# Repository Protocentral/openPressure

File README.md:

# Protocentral OpenPressure

OpenPressure is a result of our work in trying to interface pressure sensors to an ADC as well as a display system based on Arduino. We found the ADS1220 to be a great chip that can directly take a 4-wire, 3-wire or a 2-wire sensor and give the digital output. 

Combine this powerful functionality with an ATSAMD21 micro-controller and you've got your very own Arduino-compatible pressure and temperature sensor interface system.

Features
--------
* TI ADS1220 24-bit ADC
* 4-wire sensor can be interfaced directly to the inputs
* On-board 5V band-gap voltage reference
* ATSAMD21 microcontroller loaded with Arduino M0/Zero bootloader
* Programmable with the Arduino IDE
* USB CDC Interface for data transfer
* "Cap" compatibility to add Bluetooth/WiFi/SD Card interfaces
* On-board 3.7V Li-Poly battery with charger
* On-board Boost DC/DC converter 

Repository Contents
-------------------
* **/hardware** - All Eagle design files (.brd, .sch)
* **/software** - Arduino libraries and example code
* **/docs** - Additional Documentation

Board Overview
--------------

How to setup Arduino support for openPressure
---------------------------------------------------
OpenPressure is powered by the Arduino Zero board support file.The first thing you will need to do is to download the latest release of the Arduino IDE. You will need to be using version 1.6.4 or higher. 

If you want to program your Zero while offline you need to install the Arduino Desktop IDE and add the Atmel SAMD Core to it. This simple procedure is done selecting Tools menu, then Boards and last Boards Manager, as documented in the Arduino Boards Manager page. 

* Select Tools > Board > Board Manager
* You should find Arduino SAMD(32-bit ARM cortex-M0+) boards listed in the Board Manager window.

* Click the “Install” button on the chosen category.The download process will begin and install the toolchain for SAMD microcontrollers.
* Restart Arduino and look under Tools > Boards and you should see the addition of the Arduino boards in your board list.

Setup Arduino Sketch
--------------------
We have provided a few Arduino sketch examples . They are designed to work right away with no changes. To make the examples work with your board, you simply need to upload the code to your board.

License Information
-------------------
This product is open source!

Please use, reuse, and modify these files as you see fit. Please maintain attribution to Protocentral and release anything derivative under the same license.

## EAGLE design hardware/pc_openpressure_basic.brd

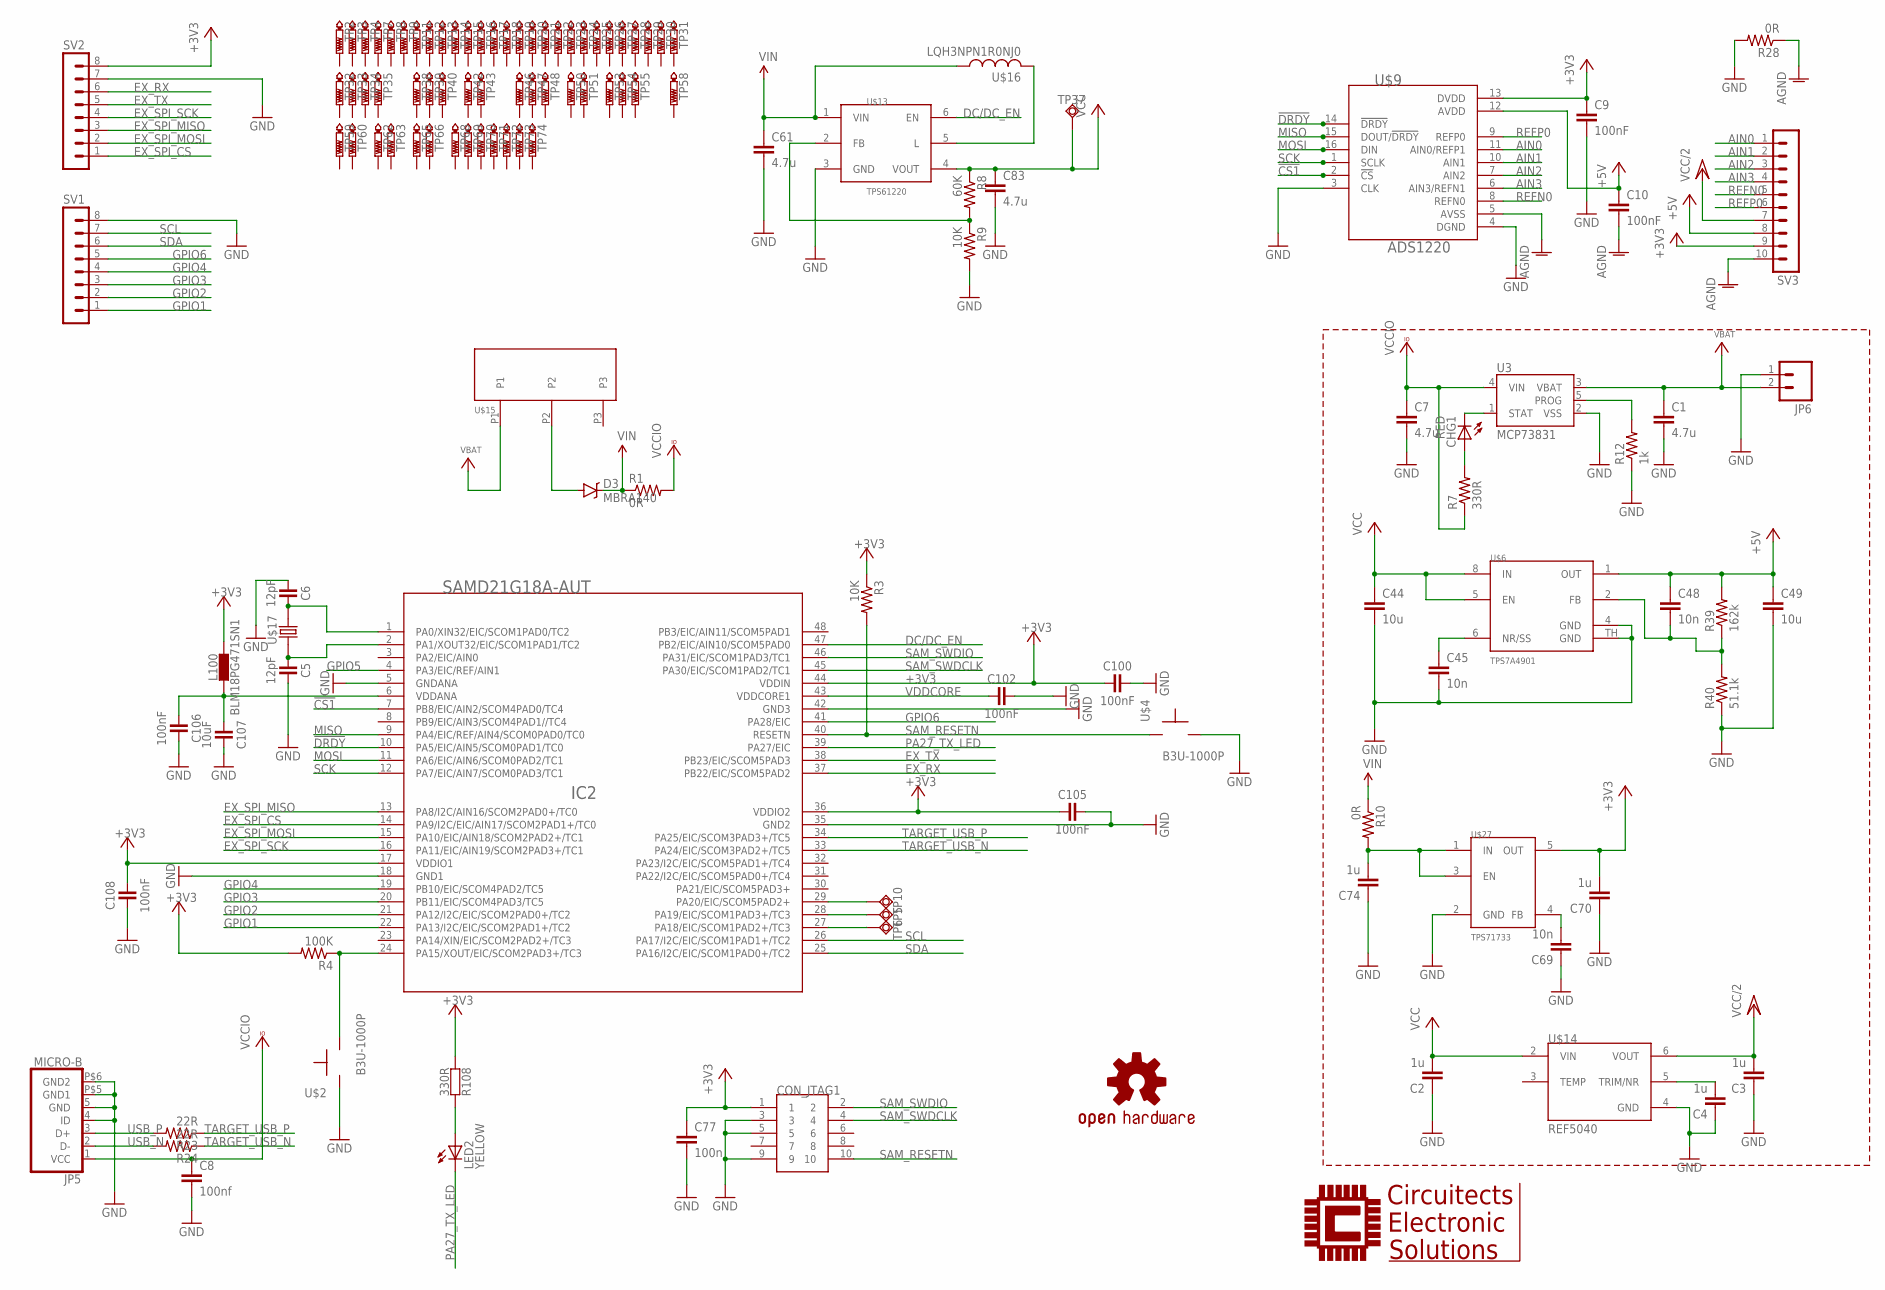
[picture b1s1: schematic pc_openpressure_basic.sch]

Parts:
C1, C7, C61, C83: 4.7u; C0805
C2, C3, C4, C70, C74: 1u; C0805
C5, C6: 12pF; C0402
C8: 100nf; C0805
C9, C10, C100, C102, C105, C106, C108: 100nF; C0805
C44, C49: 10u; C0805
C45, C48, C69: 10n; C0402
C77: 100n; C0805
C107: 10uF; C0805
CHG1: RED; CHIPLED_0603
CON_JTAG1: HDR-SMT-50MIL/5X2
D3: MBRA140; SMA-DIODE
IC2: SAMD21G18A-AUT; TQFP48
JP5: MICRO-B
JP6: M02-JST-2MM-SMT; JST-2-SMD
L100: BLM18PG471SN1; C0603
LED2: YELLOW; CHIPLED_0603
R1, R10: 0R; R0402
R3, R9: 10K; R0805
R4: 100K; R0402
R7: 330R; R0805
R8: 60K; R0805
R12: 1k; R0805
R23, R24: 22R; R0402
R28: 0R; R0805
R39: 162k; R0805
R40: 51.1k; R0805
R108: 330R; C0402
SV1, SV2: MA08-1
SV3: MA10-1
TP2, TP3, TP4, TP7, TP8, TP9, TP11, TP12, TP13, TP14, TP15, TP16, TP17, TP18, TP19, TP20, TP21, TP22, TP23, TP24, TP25, TP26, TP27, TP28, TP29, TP30, TP31, TP32, TP33, TP34, TP35, TP38, TP39, TP40, TP42, TP43, TP46, TP47, TP48, TP50, TP51, TP53, TP54, TP55, TP58, TP59, TP60, TP62, TP63, TP65, TP66, TP68, TP69, TP70, TP71, TP72, TP73, TP74: PTR1PAD1-13; P1-13
TP5, TP6, TP10, TP37: TPSQB1,27; B1,27
U3: MCP73831; SOT23-5
U$2, U$4: B3U-1000P
U$6: TPS7A4901; S-PDSO-G08
U$7: CES-LOGO; CES-LOGO-SMALL
U$8: PROTY-LOGO; LOGO-PROTY
U$9: ADS1220; TSSOP-16
U$13: TPS61220; SC-70-6
U$14: REF5040; SO-08M
U$15: PCM12SMTR
U$16: LQH3NPN1R0NJ0; LQH3NP
U$17: ECS-X-34B; ECX-31B
U$18: PROTY_LOGO_WITH_TEXT; PROTY_WITH_TEXT
U$19: OSHW-LOGOM; OSHW-LOGO-M
U$27: TPS71733; SC70-5

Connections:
!CS1: IC2.7 (PB8/EIC/AIN2/SCOM4PAD0/TC4), U$9.2 (!CS)
!DRDY: IC2.10 (PA5/EIC/AIN5/SCOM0PAD1/TC0), U$9.14 (!DRDY)
+3V3: C9.1, C70.2, C77.1, C100.1, C105.1, C108.2, CON_JTAG1.1, IC2.17 (VDDIO1), IC2.36 (VDDIO2), IC2.44 (VDDIN), L100.2, R3.1, R4.2, R108.1, SV2.8, SV3.9, U$9.13 (DVDD), U$27.5 (OUT)
+5V: C10.1, C48.1, C49.1, R39.2, SV3.8, U$6.1 (OUT), U$9.12 (AVDD)
AGND: C10.2, R28.1, SV3.10, U$9.5 (AVSS)
AIN0: SV3.1, U$9.11 (AIN0/REFP1)
AIN1: SV3.2, U$9.10 (AIN1)
AIN2: SV3.3, U$9.7 (AIN2)
AIN3: SV3.4, U$9.6 (AIN3/REFN1)
DC/DC_EN: IC2.47 (PB2/EIC/AIN10/SCOM5PAD0), U$13.6 (EN)
EX_RX: IC2.37 (PB22/EIC/SCOM5PAD2), SV2.6
EX_SPI_CS: IC2.14 (PA9/I2C/EIC/AIN17/SCOM2PAD1+/TC0), SV2.1
EX_SPI_MISO: IC2.13 (PA8/I2C/AIN16/SCOM2PAD0+/TC0), SV2.3
EX_SPI_MOSI: IC2.15 (PA10/EIC/AIN18/SCOM2PAD2+/TC1), SV2.2
EX_SPI_SCK: IC2.16 (PA11/EIC/AIN19/SCOM2PAD3+/TC1), SV2.4
EX_TX: IC2.38 (PB23/EIC/SCOM5PAD3), SV2.5
GND: C1.2, C2.1, C3.1, C4.1, C5.2, C6.1, C7.2, C8.2, C9.2, C44.2, C45.2, C49.2, C61.2, C69.1, C70.1, C74.1, C77.2, C83.2, C100.2, C102.2, C105.2, C106.2, C107.2, C108.1, CON_JTAG1.3, CON_JTAG1.5, CON_JTAG1.9, IC2.5 (GNDANA), IC2.18 (GND1), IC2.35 (GND2), IC2.42 (GND3), JP5.4 (ID), JP5.5 (GND), JP5.P$5 (GND1), JP5.P$6 (GND2), JP6.1, R9.2, R12.1, R28.2, R40.1, SV1.8, SV2.7, U3.2 (VSS), U$2.P$1, U$4.P$2, U$6.4 (GND), U$6.TH (GND), U$9.3 (CLK), U$9.4 (DGND), U$13.3 (GND), U$14.4 (GND), U$27.2 (GND)
GPIO1: IC2.22 (PA13/I2C/EIC/SCOM2PAD1+/TC2), SV1.1
GPIO2: IC2.21 (PA12/I2C/EIC/SCOM2PAD0+/TC2), SV1.2
GPIO3: IC2.20 (PB11/EIC/SCOM4PAD3/TC5), SV1.3
GPIO4: IC2.19 (PB10/EIC/SCOM4PAD2/TC5), SV1.4
GPIO5: IC2.4 (PA3/EIC/REF/AIN1)
GPIO6: IC2.41 (PA28/EIC), SV1.5
MISO: IC2.9 (PA4/EIC/REF/AIN4/SCOM0PAD0/TC0), U$9.15 (DOUT/!DRDY)
MOSI: IC2.11 (PA6/EIC/AIN6/SCOM0PAD2/TC1), U$9.16 (DIN)
unnamed: C6.2, IC2.1 (PA0/XIN32/EIC/SCOM1PAD0/TC2), U$17.P$2 (2)
unnamed: C74.2, R10.2, U$27.1 (IN), U$27.3 (EN)
unnamed: D3.A, U$15.P2
unnamed: R8.2, R9.1, U$13.2 (FB)
unnamed: IC2.24 (PA15/XOUT/EIC/SCOM2PAD3+/TC3), R4.1, U$2.P$2
unnamed: C5.1, IC2.2 (PA1/XOUT32/EIC/SCOM1PAD1/TC2), U$17.P$1 (1)
unnamed: C106.1, C107.1, IC2.6 (VDDANA), L100.1
unnamed: IC2.27 (PA18/EIC/SCOM1PAD2+/TC3), TP6.TP
unnamed: CHG1.C, U3.1 (STAT)
unnamed: CHG1.A, R7.2
unnamed: C45.1, U$6.6 (NR/SS)
unnamed: IC2.28 (PA19/EIC/SCOM1PAD3+/TC3), TP5.TP
unnamed: IC2.29 (PA20/EIC/SCOM5PAD2+), TP10.TP
unnamed: R12.2, U3.5 (PROG)
unnamed: LED2.A, R108.2
unnamed: C48.2, R39.1, R40.2, U$6.2 (FB)
unnamed: C4.2, U$14.5 (TRIM/NR)
unnamed: U$13.5 (L), U$16.P$2 (2)
unnamed: C69.2, U$27.4 (FB)
PA27_TX_LED: IC2.39 (PA27/EIC), LED2.C
REFN0: SV3.5, U$9.8 (REFN0)
REFP0: SV3.6, U$9.9 (REFP0)
SAM_RESETN: CON_JTAG1.10, IC2.40 (RESETN), R3.2, U$4.P$1
SAM_SWDCLK: CON_JTAG1.4, IC2.45 (PA30/EIC/SCOM1PAD2/TC1)
SAM_SWDIO: CON_JTAG1.2, IC2.46 (PA31/EIC/SCOM1PAD3/TC1)
SCK: IC2.12 (PA7/EIC/AIN7/SCOM0PAD3/TC1), U$9.1 (SCLK)
SCL: IC2.26 (PA17/I2C/EIC/SCOM1PAD1+/TC2), SV1.7
SDA: IC2.25 (PA16/I2C/EIC/SCOM1PAD0+/TC2), SV1.6
TARGET_USB_N: IC2.33 (PA24/EIC/SCOM3PAD2+/TC5), R24.1
TARGET_USB_P: IC2.34 (PA25/EIC/SCOM3PAD3+/TC5), R23.1
USB_N: JP5.2 (D-), R24.2
USB_P: JP5.3 (D+), R23.2
VBAT: C1.1, JP6.2, U3.3 (VBAT), U$15.P1
VCC: C2.2, C44.1, C83.1, R8.1, TP37.TP, U$6.5 (EN), U$6.8 (IN), U$13.4 (VOUT), U$14.2 (VIN)
VCC/2: C3.2, SV3.7, U$14.6 (VOUT)
VCCIO: C7.1, C8.1, JP5.1 (VCC), R1.2, R7.1, U3.4 (VIN)
VDDCORE: C102.1, IC2.43 (VDDCORE1)
VIN: C61.1, D3.C, R1.1, R10.1, U$13.1 (VIN), U$16.P$1 (1)

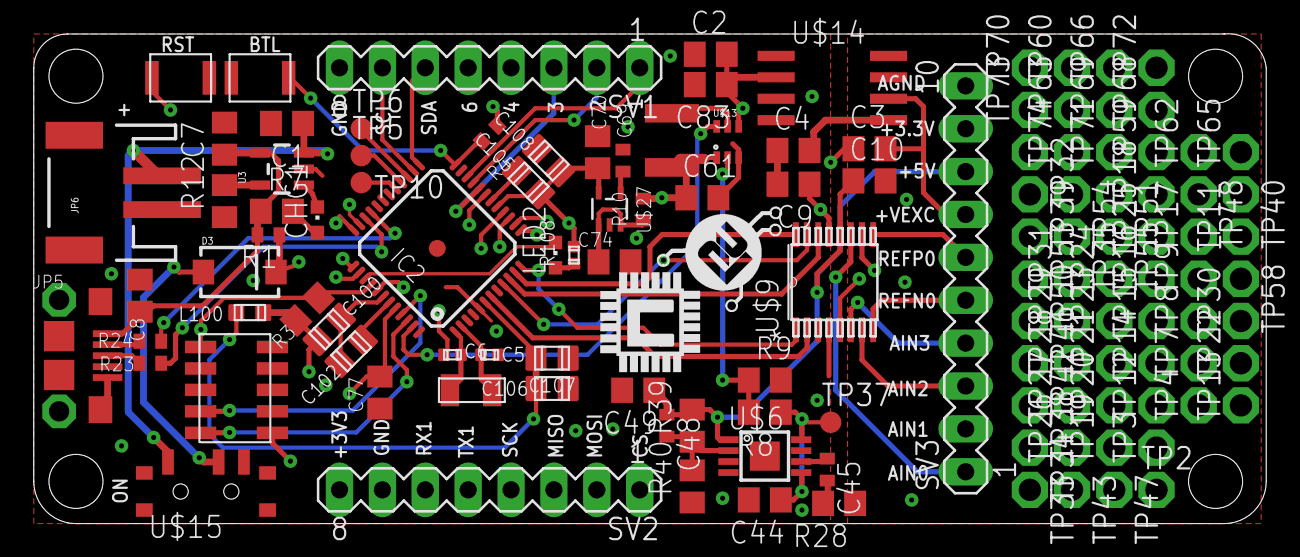
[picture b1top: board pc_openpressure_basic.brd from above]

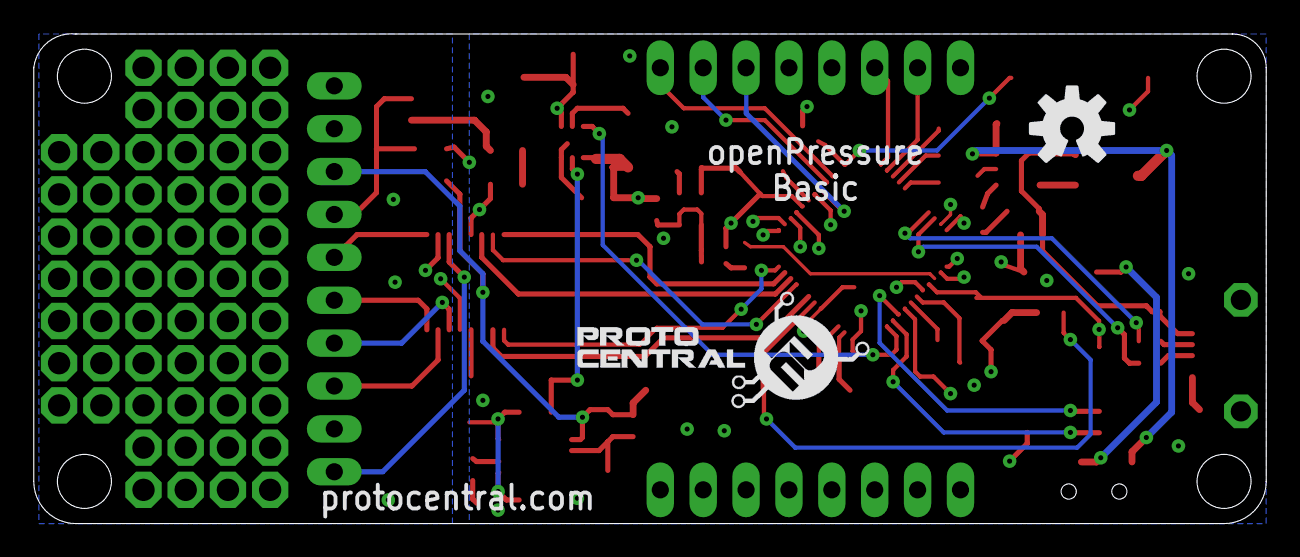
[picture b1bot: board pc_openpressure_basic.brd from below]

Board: 4 copper layers, 73.0 x 29.0 mm, 128 parts (2 on the bottom side), 62 nets.

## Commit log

2017-01-19 :boom::camel: Added .gitattributes & .gitignore files
2017-01-19 Measures pressure based on 0-2Bar pressure, code optimization yet to do
2017-02-07 updated image
2017-02-07 added image
2017-02-10 Updated Readme and images
2017-02-10 Update Readme and directory structure
2017-02-17 Updated Arduino Examples

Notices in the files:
parts and their libraries:
SparkFun-DiscreteSemi: Licensing: Creative Commons ShareAlike 4.0 International - https://creativecommons.org/licenses/by-sa/4.0
